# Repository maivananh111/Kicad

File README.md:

# Kicad
kicad board

kicad stm32

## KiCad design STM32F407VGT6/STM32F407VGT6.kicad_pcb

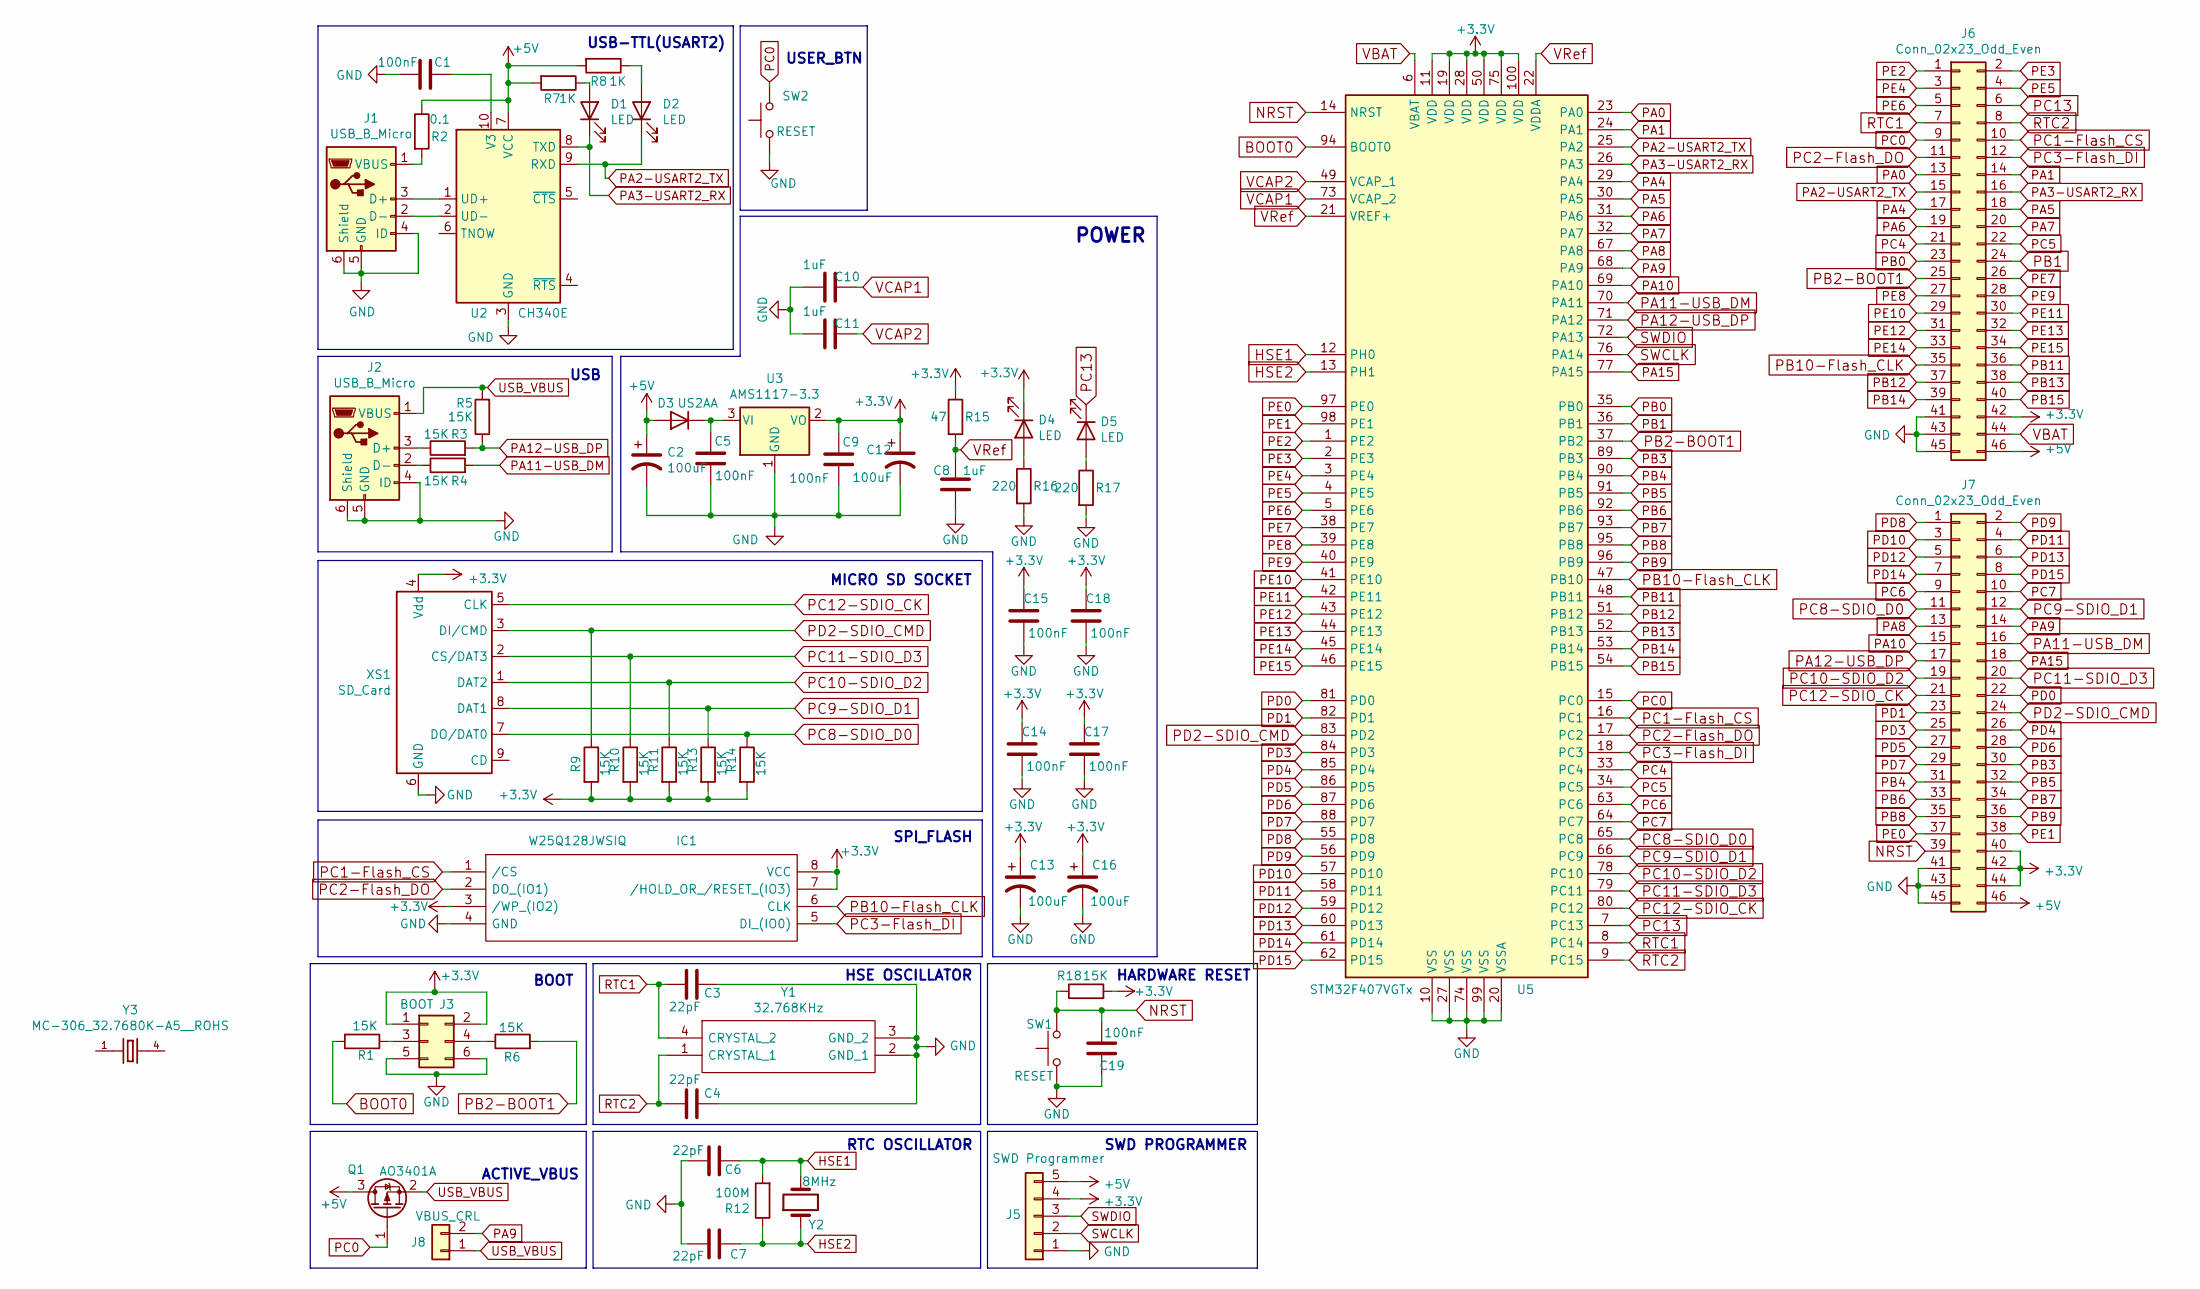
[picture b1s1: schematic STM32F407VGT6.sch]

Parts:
C1, C5, C9, C14, C15, C17, C18, C19: 100nF; C_0805_2012Metric
C2, C12, C13: 100uF; C_1210_3225Metric
C3, C4, C6, C7: 22pF; C_0805_2012Metric
C8, C10, C11: 1uF; C_0805_2012Metric
C16: 100uF; C_0805_2012Metric
D1, D2, D4, D5: LED; LED_0805_2012Metric
D3: US2AA; D_SMA
IC1: W25Q128JWSIQ; SOIC127P790X216-8N; Manufacturer_Part_Number W25Q128JWSIQ; Mouser Part Number 454-W25Q128JWSIQ
J1, J2: USB_B_Micro; USB_Micro-B_Amphenol_10104110_Horizontal
J3: BOOT; PinHeader_2x03_P2.54mm_Vertical
J5: SWD Programmer; PinHeader_1x05_P2.54mm_Horizontal
J6, J7: Conn_02x23_Odd_Even; PinHeader_2x23_P2.54mm_Vertical
J8: VBUS_CRL; PinHeader_1x02_P2.54mm_Vertical
Q1: AO3401A; SOT-23
R1, R3, R4, R5, R6, R9, R10, R11, R13, R14, R18: 15K; R_0805_2012Metric
R2: 0.1; R_1210_3225Metric_Pad1.30x2.65mm_HandSolder
R7, R8: 1K; R_0805_2012Metric
R12: 100M; R_0805_2012Metric
R15: 47; R_0805_2012Metric
R16, R17: 220; R_0805_2012Metric
SW1, SW2: RESET; SW_SPST_CK_RS282G05A3
U2: CH340E; MSOP-10_3x3mm_P0.5mm
U3: AMS1117-3.3; SOT-223-3_TabPin2
U5: STM32F407VGTx; LQFP-100_14x14mm_P0.5mm
XS1: SD_Card; Conn_uSDcard
Y1: 32.768KHz; MC306327680KE3ROHS; Manufacturer_Part_Number MC-306 32.7680K-E3:ROHS; Mouser Part Number 732-MC30632.768K-E3R
Y2: 8MHz; Crystal_HC49-4H_Vertical
Y3: MC-306_32.7680K-A5__ROHS

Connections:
+3V3: C9.1, C12.1, C13.1, C14.1, C15.1, C16.1, C17.1, C18.1, D4.1 (K), IC1.3 (/WP_(IO2)), IC1.7 (/HOLD_OR_/RESET_(IO3)), IC1.8 (VCC), J3.1, J3.2, J5.4, J6.42, J7.40, J7.42, J7.44, R9.2, R10.2, R11.2, R13.2, R14.2, R15.1, R18.2, U3.2 (VO), U5.11 (VDD), U5.19 (VDD), U5.28 (VDD), U5.50 (VDD), U5.75 (VDD), U5.100 (VDD), XS1.4 (Vdd)
+5V: C2.1, D3.2 (A), J5.5, J6.46, J7.46, Q1.3 (D), R2.1, R7.2, R8.2, U2.7 (VCC)
BOOT0: R1.2, U5.94 (BOOT0)
GND: C1.2, C2.2, C3.1, C4.1, C5.2, C6.1, C7.1, C8.2, C9.2, C10.1, C11.1, C12.2, C13.2, C14.2, C15.2, C16.2, C17.2, C18.2, C19.2, IC1.4 (GND), J1.4 (ID), J1.5 (GND), J1.6 (Shield), J2.4 (ID), J2.5 (GND), J2.6 (Shield), J3.5, J3.6, J5.1, J6.41, J6.43, J6.45, J7.41, J7.43, J7.45, R16.2, R17.2, SW1.1, SW2.1, U2.3 (GND), U3.1 (GND), U5.10 (VSS), U5.20 (VSSA), U5.27 (VSS), U5.74 (VSS), U5.99 (VSS), XS1.6 (GND), Y1.2 (GND_1), Y1.3 (GND_2); also elsewhere on the board
HSE1: C6.2, R12.2, U5.12 (PH0), Y2.2
HSE2: C7.2, R12.1, U5.13 (PH1), Y2.1
NRST: C19.1, J7.39, R18.1, SW1.2, U5.14 (NRST)
unnamed: C1.1, U2.10 (V3)
unnamed: C5.1, D3.1 (K), U3.3 (VI)
unnamed: D1.2 (A), R7.1
unnamed: D2.2 (A), R8.1
unnamed: D4.2 (A), R16.1
unnamed: D5.2 (A), R17.1
unnamed: J1.1 (VBUS), R2.2
unnamed: J1.2 (D-), U2.2 (UD-)
unnamed: J1.3 (D+), U2.1 (UD+)
unnamed: J2.2 (D-), R4.1
unnamed: J2.3 (D+), R3.1
unnamed: J3.3, R1.1
unnamed: J3.4, R6.1
PA0: J6.13, U5.23 (PA0)
PA1: J6.14, U5.24 (PA1)
PA2-USART2_TX: D2.1 (K), J6.15, U2.9 (RXD), U5.25 (PA2)
PA3-USART2_RX: D1.1 (K), J6.16, U2.8 (TXD), U5.26 (PA3)
PA4: J6.17, U5.29 (PA4)
PA5: J6.18, U5.30 (PA5)
PA6: J6.19, U5.31 (PA6)
PA7: J6.20, U5.32 (PA7)
PA8: J7.13, U5.67 (PA8)
PA9: J7.14, J8.2, U5.68 (PA9)
PA10: J7.15, U5.69 (PA10)
PA11-USB_DM: J7.16, R4.2, U5.70 (PA11)
PA12-USB_DP: J7.17, R3.2, R5.1, U5.71 (PA12)
PA15: J7.18, U5.77 (PA15)
PB0: J6.23, U5.35 (PB0)
PB1: J6.24, U5.36 (PB1)
PB2-BOOT1: J6.25, R6.2, U5.37 (PB2)
PB3: J7.30, U5.89 (PB3)
PB4: J7.31, U5.90 (PB4)
PB5: J7.32, U5.91 (PB5)
PB6: J7.33, U5.92 (PB6)
PB7: J7.34, U5.93 (PB7)
PB8: J7.35, U5.95 (PB8)
PB9: J7.36, U5.96 (PB9)
PB10-Flash_CLK: IC1.6 (CLK), J6.35, U5.47 (PB10)
PB11: J6.36, U5.48 (PB11)
PB12: J6.37, U5.51 (PB12)
PB13: J6.38, U5.52 (PB13)
PB14: J6.39, U5.53 (PB14)
PB15: J6.40, U5.54 (PB15)
PC0: J6.9, Q1.1 (G), SW2.2, U5.15 (PC0)
PC1-Flash_CS: IC1.1 (/CS), J6.10, U5.16 (PC1)
PC2-Flash_DO: IC1.2 (DO_(IO1)), J6.11, U5.17 (PC2)
PC3-Flash_DI: IC1.5 (DI_(IO0)), J6.12, U5.18 (PC3)
PC4: J6.21, U5.33 (PC4)
PC5: J6.22, U5.34 (PC5)
PC6: J7.9, U5.63 (PC6)
PC7: J7.10, U5.64 (PC7)
PC8-SDIO_D0: J7.11, R14.1, U5.65 (PC8), XS1.7 (DO/DAT0)
PC9-SDIO_D1: J7.12, R13.1, U5.66 (PC9), XS1.8 (DAT1)
PC10-SDIO_D2: J7.19, R11.1, U5.78 (PC10), XS1.1 (DAT2)
PC11-SDIO_D3: J7.20, R10.1, U5.79 (PC11), XS1.2 (CS/DAT3)
PC12-SDIO_CK: J7.21, U5.80 (PC12), XS1.5 (CLK)
PC13: D5.1 (K), J6.6, U5.7 (PC13)
PD0: J7.22, U5.81 (PD0)
PD1: J7.23, U5.82 (PD1)
PD2-SDIO_CMD: J7.24, R9.1, U5.83 (PD2), XS1.3 (DI/CMD)
PD3: J7.25, U5.84 (PD3)
PD4: J7.26, U5.85 (PD4)
PD5: J7.27, U5.86 (PD5)
PD6: J7.28, U5.87 (PD6)
PD7: J7.29, U5.88 (PD7)
PD8: J7.1, U5.55 (PD8)
PD9: J7.2, U5.56 (PD9)
PD10: J7.3, U5.57 (PD10)
PD11: J7.4, U5.58 (PD11)
PD12: J7.5, U5.59 (PD12)
PD13: J7.6, U5.60 (PD13)
PD14: J7.7, U5.61 (PD14)
PD15: J7.8, U5.62 (PD15)
PE0: J7.37, U5.97 (PE0)
PE1: J7.38, U5.98 (PE1)
PE2: J6.1, U5.1 (PE2)
PE3: J6.2, U5.2 (PE3)
PE4: J6.3, U5.3 (PE4)
PE5: J6.4, U5.4 (PE5)
PE6: J6.5, U5.5 (PE6)
PE7: J6.26, U5.38 (PE7)
PE8: J6.27, U5.39 (PE8)
PE9: J6.28, U5.40 (PE9)
PE10: J6.29, U5.41 (PE10)
PE11: J6.30, U5.42 (PE11)
PE12: J6.31, U5.43 (PE12)
PE13: J6.32, U5.44 (PE13)
PE14: J6.33, U5.45 (PE14)
PE15: J6.34, U5.46 (PE15)
RTC1: C3.2, J6.7, U5.8 (PC14), Y1.4 (CRYSTAL_2)
RTC2: C4.2, J6.8, U5.9 (PC15), Y1.1 (CRYSTAL_1)
SWCLK: J5.2, U5.76 (PA14)
SWDIO: J5.3, U5.72 (PA13)
USB_VBUS: J2.1 (VBUS), J8.1, Q1.2 (S), R5.2
VBAT: J6.44, U5.6 (VBAT)
VCAP1: C10.2, U5.73 (VCAP_2)
VCAP2: C11.2, U5.49 (VCAP_1)
VRef: C8.1, R15.2, U5.21 (VREF+), U5.22 (VDDA)

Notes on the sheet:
HSE OSCILLATOR
SWD PROGRAMMER
HARDWARE RESET
RTC OSCILLATOR
MICRO SD SOCKET
USB
POWER
ACTIVE_VBUS
SPI_FLASH
USB-TTL(USART2)
BOOT
USER_BTN

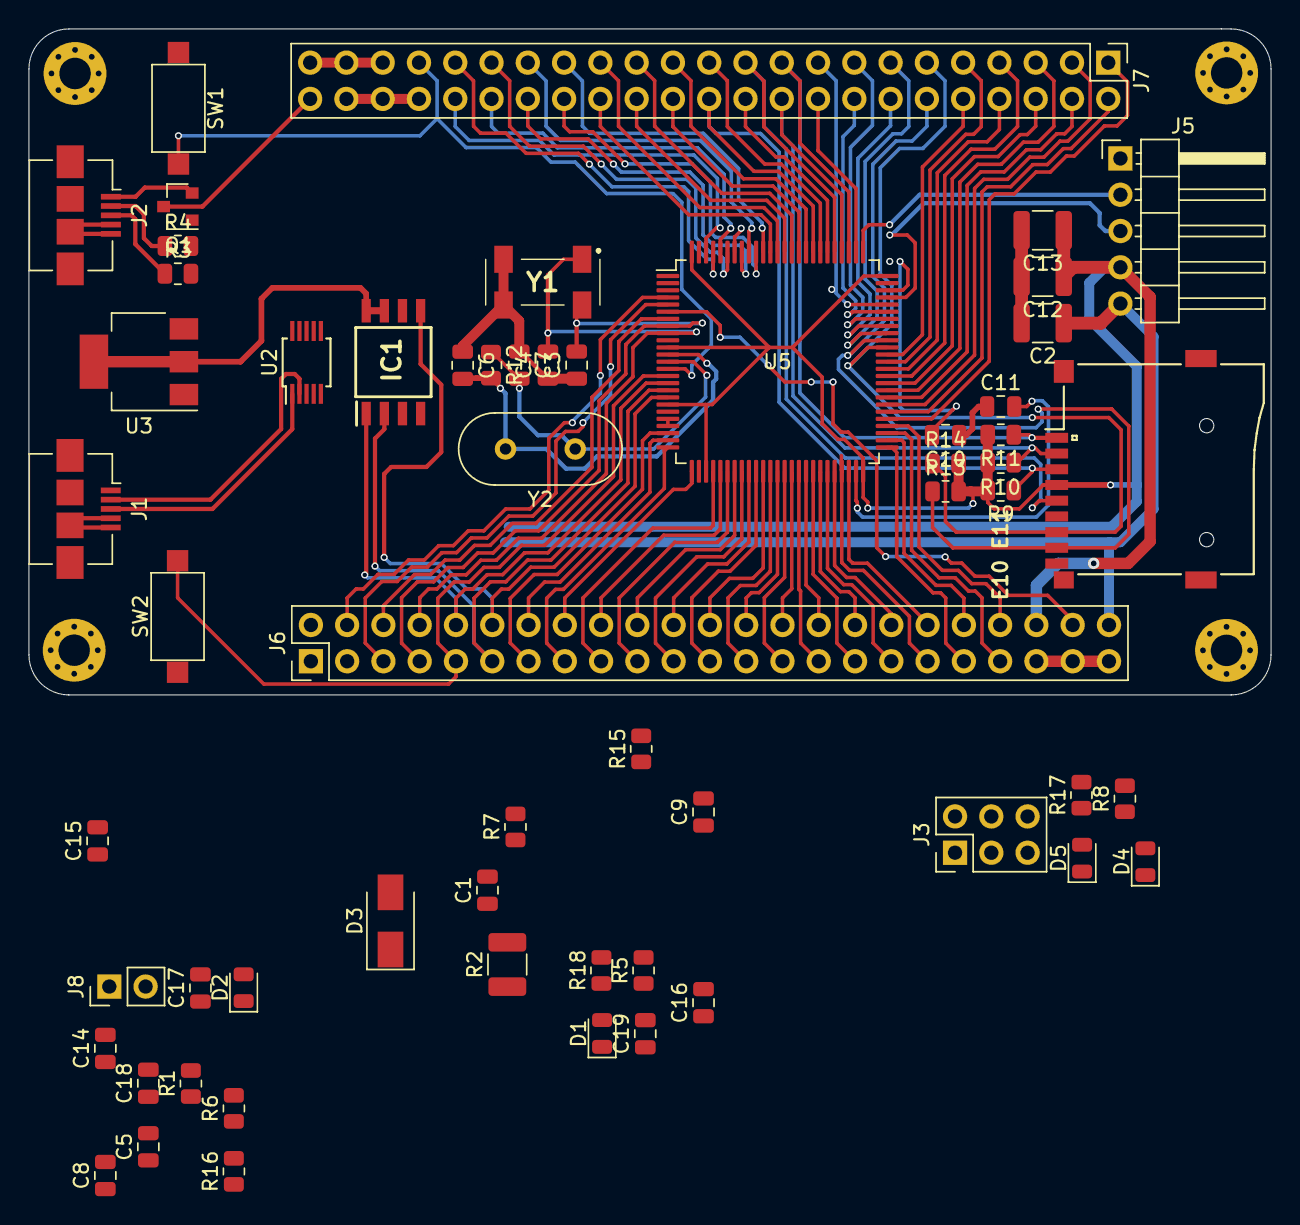
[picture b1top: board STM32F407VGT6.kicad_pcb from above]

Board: 2 copper layers, 87.0 x 46.6 mm, 63 parts (0 on the bottom side), 105 nets.

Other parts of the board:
 : MountingHole_2.2mm_M2_Pad_Via
 #2,  #3,  #4: MountingHole_2.2mm_M2_Pad_Via

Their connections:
GND: .GND, #2.GND, #3.GND, #4.GND; also elsewhere on the board

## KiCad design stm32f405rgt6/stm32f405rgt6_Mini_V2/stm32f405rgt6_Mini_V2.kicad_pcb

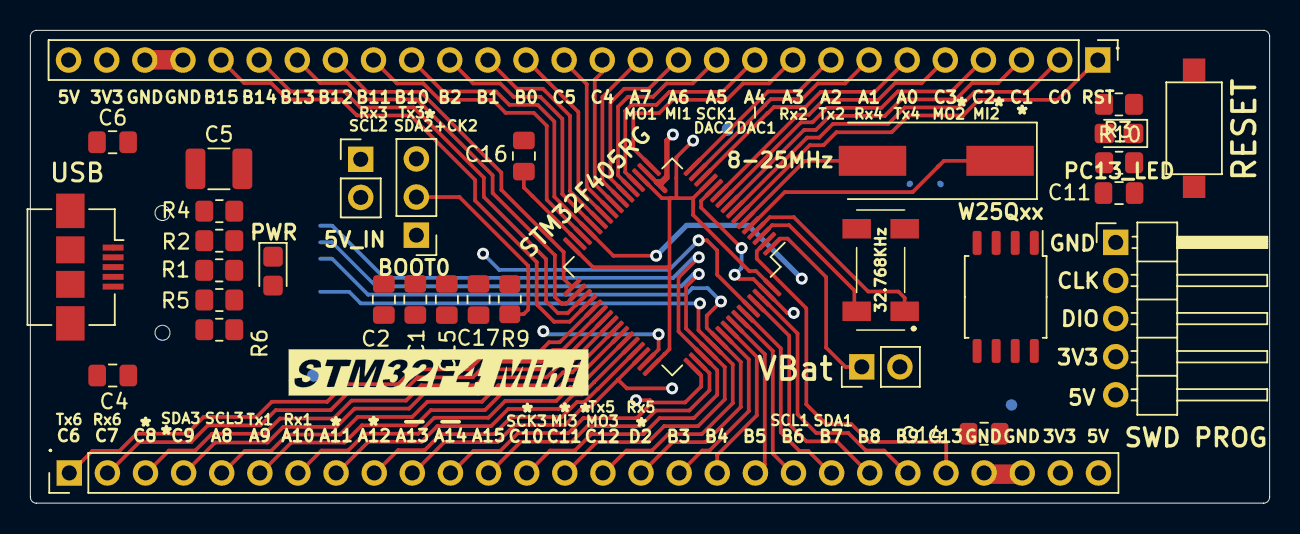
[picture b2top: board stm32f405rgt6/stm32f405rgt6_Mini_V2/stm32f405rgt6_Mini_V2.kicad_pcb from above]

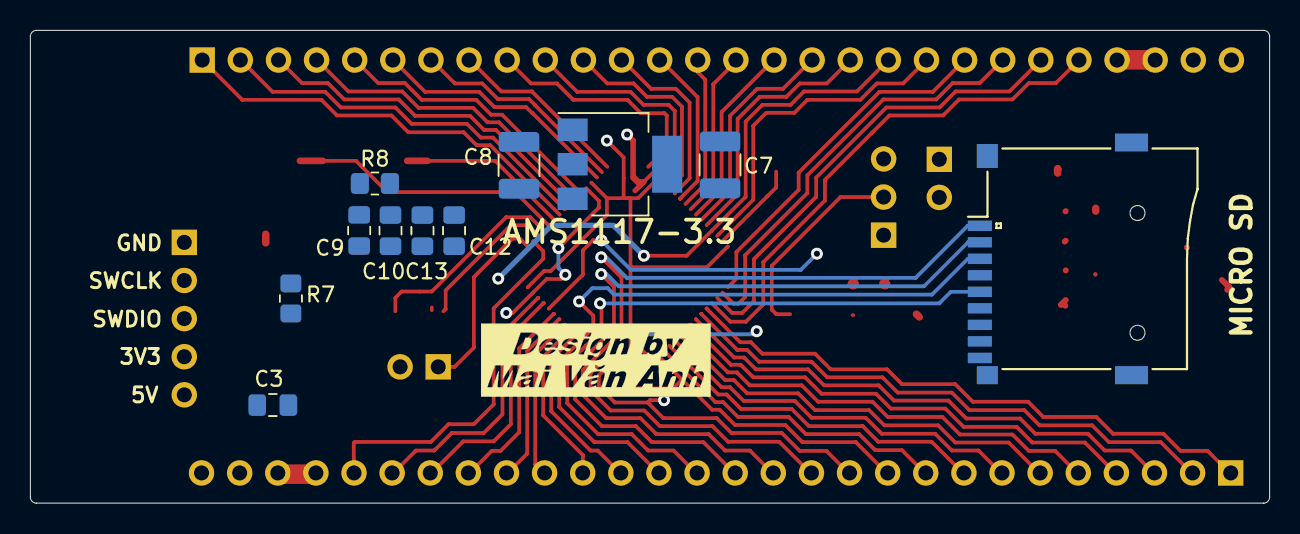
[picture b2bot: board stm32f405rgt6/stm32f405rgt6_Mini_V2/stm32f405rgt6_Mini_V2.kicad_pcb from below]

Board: 2 copper layers, 82.6 x 31.5 mm, 45 parts (12 on the bottom side), 65 nets.

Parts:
5V_IN: 5V buck; PinHeader_1x02_P2.54mm_Vertical
8-25MHz: 8MHz; Crystal_SMD_HC49-SD
32.768KHz: 32.768KHz; MC306327680KE3ROHS
.: Design
.#2: .; STM32F4 Mini
.#3: Con_B; PinHeader_1x28_P2.54mm_Vertical
.#4: Con_A; PinHeader_1x28_P2.54mm_Vertical
AMS1117-3.3: AP1117-33; SOT-223-3_TabPin2
BOOT0: BOOT; PinHeader_1x03_P2.54mm_Vertical
C1, C2, C3, C4, C6, C11, C14, C15, C16, C17: 100nF; C_0805_2012Metric_Pad1.18x1.45mm_HandSolder
C5, C7, C8: 100uF; C_1210_3225Metric_Pad1.33x2.70mm_HandSolder
C9, C10, C12, C13: 22pF; C_0805_2012Metric_Pad1.18x1.45mm_HandSolder
J4: Micro_SD_Card; Conn_uSDcard
PC13_LED: LED; LED_0805_2012Metric_Castellated
PWR: LED; LED_0805_2012Metric_Castellated
R1, R2: 22R; R_0805_2012Metric_Pad1.20x1.40mm_HandSolder
R3: 560; R_0805_2012Metric_Pad1.20x1.40mm_HandSolder
R4, R5: 4k7; R_0805_2012Metric_Pad1.20x1.40mm_HandSolder
R6: 150; R_0805_2012Metric_Pad1.20x1.40mm_HandSolder
R7, R9, R10: 10k; R_0805_2012Metric_Pad1.20x1.40mm_HandSolder
R8: 10M; R_0805_2012Metric_Pad1.20x1.40mm_HandSolder
RESET: Reset; SW_SPST_CK_RS282G05A3
STM32F405RG: STM32F405RGTx; LQFP-64_10x10mm_P0.5mm
SWD PROG: SWD; PinHeader_1x05_P2.54mm_Horizontal
USB: USB; USB_Micro-B_Amphenol_10104110_Horizontal
VBat: VBAT; PinHeader_1x02_P2.54mm_Vertical
W25Qxx: W25Q32JVSS; SOIC-8_5.23x5.23mm_P1.27mm

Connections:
+3V3: .#3.27, .#4.27, AMS1117-3.3.2, BOOT0.3, C1.2, C2.2, C4.2, C6.2, C7.1, C8.1, C14.2, C15.2, J4.6, PWR.1, R7.1, R10.2, STM32F405RG.13, STM32F405RG.19, STM32F405RG.32, STM32F405RG.48, STM32F405RG.64, SWD PROG.4, W25Qxx.3, W25Qxx.7, W25Qxx.8
+5V: 5V_IN.1, .#3.28, .#4.28, C3.2, C5.1, SWD PROG.5, USB.1
GND: 32.768KHz.2, 32.768KHz.3, .#3.25, .#3.26, .#4.25, .#4.26, AMS1117-3.3.1, BOOT0.1, C1.1, C2.1, C3.1, C4.1, C5.2, C6.1, C7.2, C8.2, C9.2, C10.2, C11.2, C12.2, C13.2, C14.1, C15.1, C16.2, C17.2, J4.4, J4.9, R3.1, R4.2, R5.2, R6.1, RESET.1, STM32F405RG.12, STM32F405RG.18, STM32F405RG.63, SWD PROG.1, USB.4, USB.5, USB.6, VBat.2, W25Qxx.4
unnamed: 8-25MHz.1, C9.1, R8.1, STM32F405RG.5
unnamed: 8-25MHz.2, C10.1, R8.2, STM32F405RG.6
unnamed: 32.768KHz.4, C12.1, STM32F405RG.3
unnamed: 32.768KHz.1, C13.1, STM32F405RG.4
unnamed: C16.1, STM32F405RG.31
unnamed: C17.1, STM32F405RG.47
unnamed: PC13_LED.2, R3.2
unnamed: PWR.2, R6.2
unnamed: BOOT0.2, R9.2
unnamed: R2.2, USB.2
unnamed: R1.2, USB.3
unnamed: 5V_IN.2, AMS1117-3.3.3
unnamed: R9.1, STM32F405RG.60
PA0: .#3.6, STM32F405RG.14
PA1: .#3.7, STM32F405RG.15
PA2: .#3.8, STM32F405RG.16
PA3: .#3.9, STM32F405RG.17
PA4: .#3.10, STM32F405RG.20
PA5: .#3.11, STM32F405RG.21
PA6: .#3.12, STM32F405RG.22
PA7: .#3.13, STM32F405RG.23
PA8: .#4.5, STM32F405RG.41
PA9: .#4.6, STM32F405RG.42
PA10: .#4.7, STM32F405RG.43
PA11: .#4.8, R2.1, R4.1, STM32F405RG.44
PA12: .#4.9, R1.1, R5.1, STM32F405RG.45
PA13: .#4.10, STM32F405RG.46, SWD PROG.3
PA14: .#4.11, STM32F405RG.49, SWD PROG.2
PA15: .#4.12, STM32F405RG.50
PB0: .#3.16, STM32F405RG.26
PB1: .#3.17, STM32F405RG.27
PB2: .#3.18, STM32F405RG.28
PB3: .#4.17, STM32F405RG.55
PB4: .#4.18, STM32F405RG.56
PB5: .#4.19, STM32F405RG.57
PB6: .#4.20, STM32F405RG.58
PB7: .#4.21, STM32F405RG.59
PB8: .#4.22, STM32F405RG.61
PB9: .#4.23, STM32F405RG.62
PB10: .#3.19, STM32F405RG.29, W25Qxx.6
PB11: .#3.20, STM32F405RG.30
PB12: .#3.21, STM32F405RG.33
PB13: .#3.22, STM32F405RG.34
PB14: .#3.23, STM32F405RG.35
PB15: .#3.24, STM32F405RG.36
PC0: .#3.2, STM32F405RG.8
PC1: .#3.3, R7.2, STM32F405RG.9, W25Qxx.1
PC2: .#3.4, STM32F405RG.10, W25Qxx.2
PC3: .#3.5, STM32F405RG.11, W25Qxx.5
PC4: .#3.14, STM32F405RG.24
PC5: .#3.15, STM32F405RG.25
PC6: .#4.1, STM32F405RG.37
PC7: .#4.2, STM32F405RG.38
PC8: .#4.3, J4.7, STM32F405RG.39
PC9: .#4.4, J4.8, STM32F405RG.40
PC10: .#4.13, J4.1, STM32F405RG.51
PC11: .#4.14, J4.2, STM32F405RG.52
PC12: .#4.15, J4.5, STM32F405RG.53
PC13: .#4.24, PC13_LED.1, STM32F405RG.2
PD2: .#4.16, J4.3, STM32F405RG.54
Reset: .#3.1, C11.1, R10.1, RESET.2, STM32F405RG.7
VBat: STM32F405RG.1, VBat.1

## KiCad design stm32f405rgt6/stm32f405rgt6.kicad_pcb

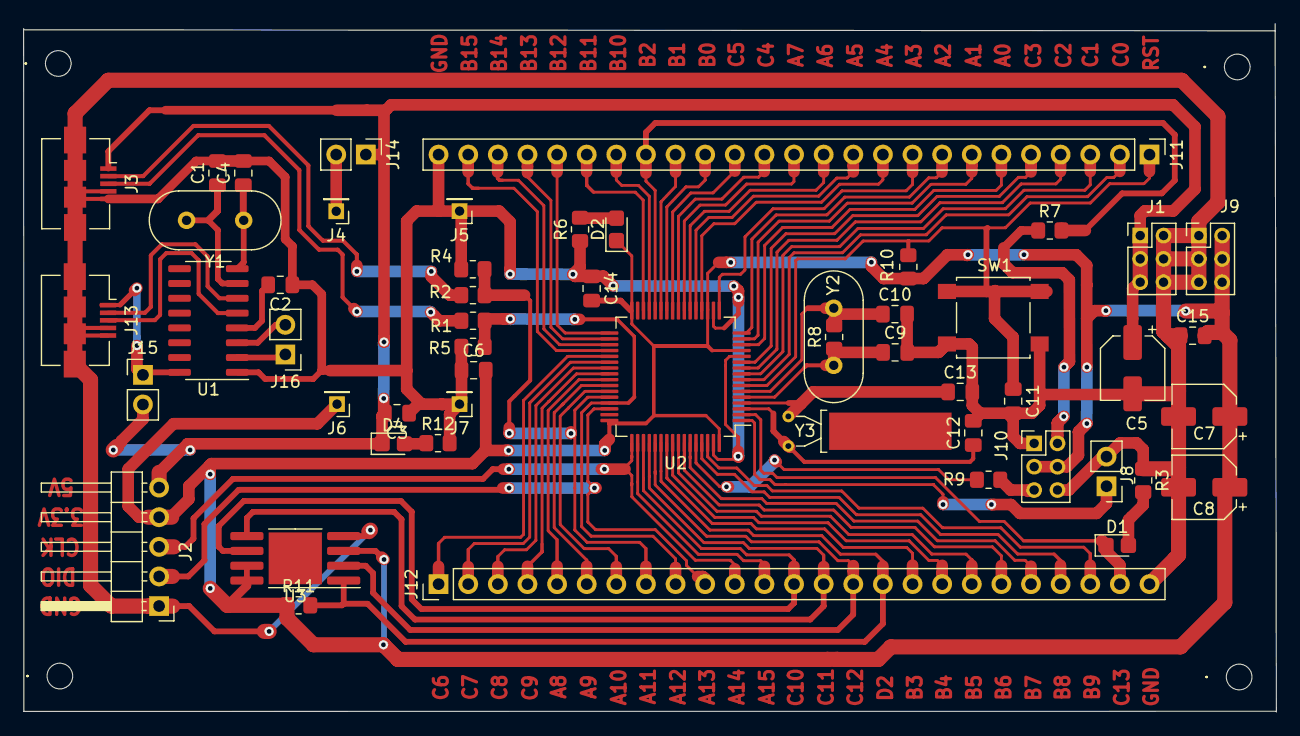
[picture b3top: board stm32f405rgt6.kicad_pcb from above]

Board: 2 copper layers, 107.4 x 59.0 mm, 57 parts (0 on the bottom side), 73 nets.

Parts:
., .#2, .#3, .#4: *; MountingHole_2.2mm_M2
C1, C4, C9, C10, C12, C13: 22pF; C_0805_2012Metric_Pad1.18x1.45mm_HandSolder
C2, C3, C6, C11, C14, C15: 100nF; C_0805_2012Metric_Pad1.18x1.45mm_HandSolder
C5, C7, C8: 100uF; CP_Elec_5x3
D1, D2, D4: LED; LED_0805_2012Metric_Castellated
J1: +5V Output; PinHeader_2x03_P2.00mm_Vertical
J2: SWD; PinHeader_1x05_P2.54mm_Horizontal
J3: USB; USB_Micro-B_Amphenol_10104110_Horizontal
J4: +5V; PinHeader_1x01_P2.00mm_Vertical
J5, J7: GND; PinHeader_1x01_P2.00mm_Vertical
J6: +3.3V; PinHeader_1x01_P2.00mm_Vertical
J8: VBAT; PinHeader_1x02_P2.54mm_Vertical
J9: +3.3V Output; PinHeader_2x03_P2.00mm_Vertical
J10: BOOT; PinHeader_2x03_P2.00mm_Vertical
J11: JB; PinHeader_1x25_P2.54mm_Vertical
J12: JA; PinHeader_1x25_P2.54mm_Vertical
J13: USB_OTG; USB_Micro-B_Amphenol_10104110_Horizontal
J14: 5V buck; PinHeader_1x02_P2.54mm_Vertical
J15: 5V conn; PinHeader_1x02_P2.54mm_Vertical
J16: UART; PinHeader_1x02_P2.54mm_Vertical
R1, R2: 22R; R_0805_2012Metric_Pad1.20x1.40mm_HandSolder
R3, R6, R12: 560; R_0805_2012Metric_Pad1.20x1.40mm_HandSolder
R4, R5: 4k7; R_0805_2012Metric_Pad1.20x1.40mm_HandSolder
R7, R9, R10, R11: 10k; R_0805_2012Metric_Pad1.20x1.40mm_HandSolder
R8: 10M; R_0805_2012Metric_Pad1.20x1.40mm_HandSolder
SW1: Reset; SW_SPST_B3S-1000
U1: CH340G; SOIC-16_3.9x9.9mm_P1.27mm
U2: STM32F405RGTx; LQFP-64_10x10mm_P0.5mm
U3: 25LCxxx; SOP-8-1EP_4.57x4.57mm_P1.27mm_EP4.57x4.45mm
Y1: 12MHz; Crystal_HC18-U_Vertical
Y2: 8MHz; Crystal_HC18-U_Vertical
Y3: 32.768MHz; Crystal_AT310_D3.0mm_L10.0mm_Horizontal_1EP_style1

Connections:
+3V3: C6.2, C7.1, C8.1, C14.2, C15.2, D2.1, J2.4, J6.1, J9.2, J9.4, J9.6, J10.3, J10.4, R10.1, R11.1, U2.13, U2.19, U2.32, U2.48, U2.64, U3.3, U3.7, U3.8
+5V: C3.2, C5.1, D4.1, J1.1, J1.3, J1.5, J2.5, J3.1, J14.1, J15.2
GND: C1.2, C2.1, C3.1, C4.2, C5.2, C6.1, C7.2, C8.2, C9.2, C10.2, C11.2, C12.2, C13.2, C14.1, C15.1, J1.2, J1.4, J1.6, J2.1, J3.4, J3.5, J3.6, J5.1, J7.1, J8.2, J9.1, J9.3, J9.5, J10.1, J10.6, J11.25, J12.25, J13.4, J13.5, J13.6, R3.1, R4.2, R5.2, R6.1, R12.2, SW1.1, U1.1, U2.12, U2.18, U2.63, U3.4
unnamed: C1.1, U1.7, Y1.2
unnamed: C2.2, U1.4
unnamed: C4.1, U1.8, Y1.1
unnamed: C9.1, R8.1, U2.5, Y2.1
unnamed: C10.1, R8.2, U2.6, Y2.2
unnamed: C12.1, U2.3, Y3.1
unnamed: C13.1, U2.4, Y3.2
unnamed: D1.2, R3.2
unnamed: D2.2, R6.2
unnamed: D4.2, R12.1
unnamed: J3.2, R2.2
unnamed: J3.3, R1.2
unnamed: J10.2, R7.1
unnamed: J10.5, R9.2
unnamed: J13.1, J15.1, U1.16
unnamed: J13.2, U1.6
unnamed: J13.3, U1.5
unnamed: J4.1, J14.2
unnamed: J16.1, U1.2
unnamed: J16.2, U1.3
unnamed: R9.1, U2.60
PA0: J11.6, U2.14
PA1: J11.7, U2.15
PA2: J11.8, U2.16
PA3: J11.9, U2.17
PA4: J11.10, U2.20
PA5: J11.11, U2.21
PA6: J11.12, U2.22
PA7: J11.13, U2.23
PA8: J12.5, U2.41
PA9: J12.6, U2.42
PA10: J12.7, U2.43
PA11: J12.8, R2.1, R4.1, U2.44
PA12: J12.9, R1.1, R5.1, U2.45
PA13: J2.2, J12.10, U2.46
PA14: J2.3, J12.11, U2.49
PA15: J12.12, U2.50
PB0: J11.16, U2.26
PB1: J11.17, U2.27
PB2: J11.18, R7.2, U2.28
PB3: J12.17, U2.55
PB4: J12.18, U2.56
PB5: J12.19, U2.57
PB6: J12.20, U2.58
PB7: J12.21, U2.59
PB8: J12.22, U2.61
PB9: J12.23, U2.62
PB10: J11.19, U2.29
PB11: J11.20, U2.30
PB12: J11.21, U2.33
PB13: J11.22, U2.34
PB14: J11.23, U2.35
PB15: J11.24, U2.36
PC0: J11.2, U2.8
PC1: J11.3, U2.9
PC2: J11.4, U2.10
PC3: J11.5, U2.11
PC4: J11.14, U2.24
PC5: J11.15, U2.25
PC6: J12.1, U2.37
PC7: J12.2, U2.38
PC8: J12.3, U2.39
PC9: J12.4, U2.40
PC10: J12.13, U2.51, U3.6
PC11: J12.14, U2.52, U3.5
PC12: J12.15, U2.53, U3.2
PC13: D1.1, J12.24, U2.2
PD2: J12.16, R11.2, U2.54, U3.1
Reset: C11.1, J11.1, R10.2, SW1.2, U2.7
VBat: J8.1, U2.1

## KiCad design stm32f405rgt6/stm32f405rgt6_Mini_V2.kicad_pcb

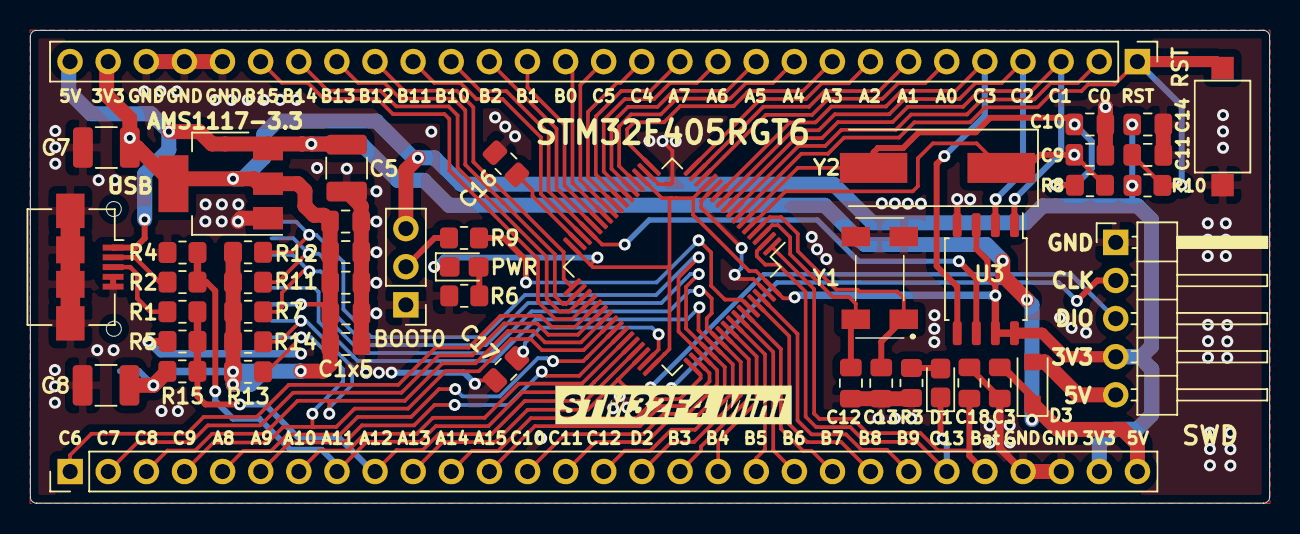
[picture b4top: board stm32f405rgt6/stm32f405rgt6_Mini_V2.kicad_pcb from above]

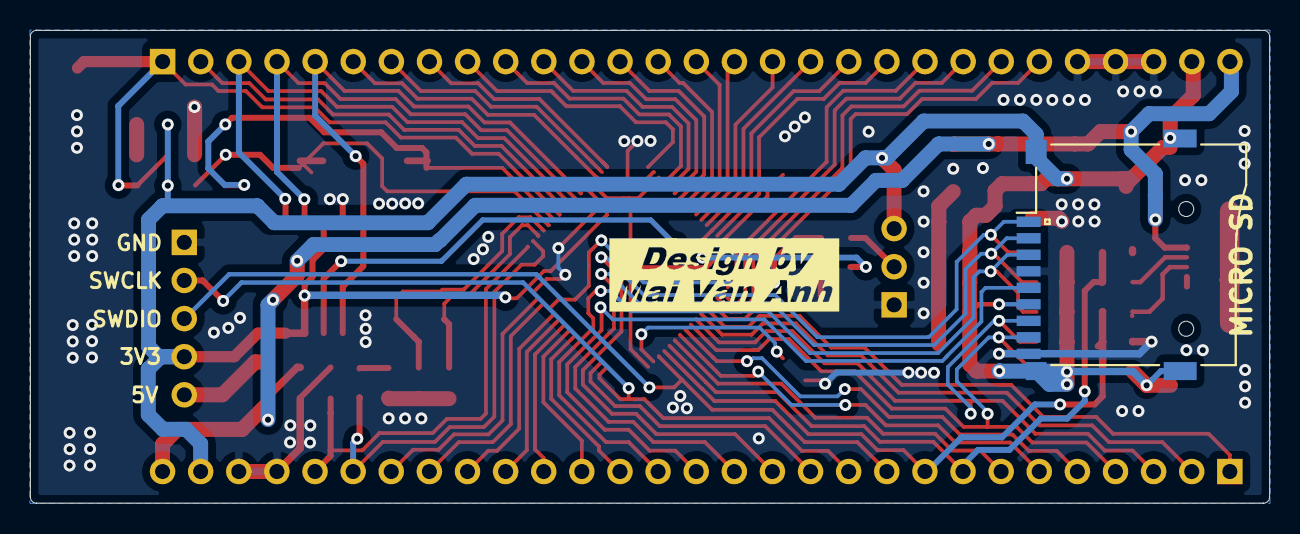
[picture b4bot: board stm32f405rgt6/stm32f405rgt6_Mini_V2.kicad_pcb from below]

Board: 2 copper layers, 82.6 x 31.5 mm, 50 parts (2 on the bottom side), 65 nets.

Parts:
 : Design
 #2: STM32F4 mini V2
 #3: STM32F405RGTx; LQFP-64_10x10mm_P0.5mm
 #4,  #5,  #6,  #7: 100nF; C_0805_2012Metric_Pad1.18x1.45mm_HandSolder
 #8: Con_B; PinHeader_1x29_P2.54mm_Vertical
 #9: Con_A; PinHeader_1x29_P2.54mm_Vertical
AMS1117-3.3: AP1117-33; SOT-223-3_TabPin2
BOOT0: BOOT; PinHeader_1x03_P2.54mm_Vertical
C1x5, C3, C11, C14, C16, C17, C18: 100nF; C_0805_2012Metric_Pad1.18x1.45mm_HandSolder
C5, C7, C8: 100uF; C_1210_3225Metric_Pad1.33x2.70mm_HandSolder
C9, C10, C12, C13: 22pF; C_0805_2012Metric_Pad1.18x1.45mm_HandSolder
D1: LED; LED_0805_2012Metric_Castellated
D3: MBR1020VL; D_SOD-123F
J4: Micro_SD_Card; Conn_uSDcard
PWR: LED; LED_0805_2012Metric_Castellated
R1, R2: 22R; R_0805_2012Metric_Pad1.20x1.40mm_HandSolder
R3: 560; R_0805_2012Metric_Pad1.20x1.40mm_HandSolder
R4, R5: 4k7; R_0805_2012Metric_Pad1.20x1.40mm_HandSolder
R6: 150; R_0805_2012Metric_Pad1.20x1.40mm_HandSolder
R7, R9, R10, R11, R12, R13, R14: 10k; R_0805_2012Metric_Pad1.20x1.40mm_HandSolder
R8: 10M; R_0805_2012Metric_Pad1.20x1.40mm_HandSolder
R15: 1k; R_0805_2012Metric_Pad1.20x1.40mm_HandSolder
RST: Reset; SW_SPST_CK_RS282G05A3
SWD : SWD; PinHeader_1x05_P2.54mm_Horizontal
U3: W25Q32JVSS; SOIC-8_5.23x5.23mm_P1.27mm
USB: USB; USB_Micro-B_Amphenol_10104110_Horizontal
Y1: 32.768KHz; MC306327680KE3ROHS
Y2: 8MHz; Crystal_SMD_HC49-SD

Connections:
+3V3: #3.13, #3.19, #3.32, #3.48, #3.64, #4.2, #5.2, #6.2, #7.2, #8.28, #9.28, AMS1117-3.3.2, BOOT0.3, C1x5.2, C7.1, C8.1, C14.2, J4.6, PWR.1, R7.1, R10.2, R11.1, R12.1, R13.1, R14.1, R15.1, SWD.4, U3.3, U3.7, U3.8
+5V: #8.29, #9.29, AMS1117-3.3.3, C3.2, C5.1, D3.1, USB.1
GND: #3.12, #3.18, #3.63, #4.1, #5.1, #6.1, #7.1, #8.25, #8.26, #8.27, #9.26, #9.27, AMS1117-3.3.1, BOOT0.1, C1x5.1, C3.1, C5.2, C7.2, C8.2, C9.2, C10.2, C11.2, C12.2, C13.2, C14.1, C16.2, C17.2, C18.1, J4.4, J4.9, R3.1, R4.2, R5.2, R6.1, RST.1, SWD.1, U3.4, USB.4, USB.5, USB.6, Y1.2, Y1.3
unnamed: #3.5, C9.1, R8.1, Y2.1
unnamed: #3.6, C10.1, R8.2, Y2.2
unnamed: #3.3, C12.1, Y1.4
unnamed: #3.4, C13.1, Y1.1
unnamed: #3.31, C16.1
unnamed: #3.47, C17.1
unnamed: D1.2, R3.2
unnamed: PWR.2, R6.2
unnamed: D3.2, SWD.5
unnamed: BOOT0.2, R9.2
unnamed: R2.2, USB.2
unnamed: R1.2, USB.3
unnamed: #3.60, R9.1
PA0: #3.14, #8.6
PA1: #3.15, #8.7
PA2: #3.16, #8.8
PA3: #3.17, #8.9
PA4: #3.20, #8.10
PA5: #3.21, #8.11
PA6: #3.22, #8.12
PA7: #3.23, #8.13
PA8: #3.41, #9.5
PA9: #3.42, #9.6
PA10: #3.43, #9.7
PA11: #3.44, #9.8, R2.1, R4.1
PA12: #3.45, #9.9, R1.1, R5.1, R15.2
PA13: #3.46, #9.10, SWD.3
PA14: #3.49, #9.11, SWD.2
PA15: #3.50, #9.12
PB0: #3.26, #8.16
PB1: #3.27, #8.17
PB2: #3.28, #8.18
PB3: #3.55, #9.17
PB4: #3.56, #9.18
PB5: #3.57, #9.19
PB6: #3.58, #9.20
PB7: #3.59, #9.21
PB8: #3.61, #9.22
PB9: #3.62, #9.23
PB10: #3.29, #8.19, U3.6
PB11: #3.30, #8.20
PB12: #3.33, #8.21
PB13: #3.34, #8.22
PB14: #3.35, #8.23
PB15: #3.36, #8.24
PC0: #3.8, #8.2
PC1: #3.9, #8.3, U3.1
PC2: #3.10, #8.4, U3.2
PC3: #3.11, #8.5, U3.5
PC4: #3.24, #8.14
PC5: #3.25, #8.15
PC6: #3.37, #9.1
PC7: #3.38, #9.2
PC8: #3.39, #9.3, J4.7, R14.2
PC9: #3.40, #9.4, J4.8, R13.2
PC10: #3.51, #9.13, J4.1, R12.2
PC11: #3.52, #9.14, J4.2, R11.2
PC12: #3.53, #9.15, J4.5
PC13: #3.2, #9.24, D1.1
PD2: #3.54, #9.16, J4.3, R7.2
Reset: #3.7, #8.1, C11.1, R10.1, RST.2
VBat: #3.1, #9.25, C18.2

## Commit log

2021-10-14 Create STM32F407-ESP8266
